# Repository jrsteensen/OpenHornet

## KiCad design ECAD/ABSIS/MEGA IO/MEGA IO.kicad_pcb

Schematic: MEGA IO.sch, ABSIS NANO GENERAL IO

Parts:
C1: 0.1uF; C_0603_HandSoldering
D1, D2, D3: 1N4001; D_1206
J1: PWR; Molex_KK-6410-04_04x2.54mm_Straight
J2: BUS IN; Molex_KK-6410-03_03x2.54mm_Straight
J3: BUS OUT; Molex_KK-6410-03_03x2.54mm_Straight
J4: PWM; Pin_Header_Straight_2x11_Pitch2.54mm
J5: DIG 1; Pin_Header_Straight_2x16_Pitch2.54mm
J6: DIG 2; Pin_Header_Straight_2x16_Pitch2.54mm
J7: A0; Pin_Header_Straight_1x03_Pitch2.54mm
J8: A1; Pin_Header_Straight_1x03_Pitch2.54mm
J9: A2; Pin_Header_Straight_1x03_Pitch2.54mm
J10: A3; Pin_Header_Straight_1x03_Pitch2.54mm
J11: A4; Pin_Header_Straight_1x03_Pitch2.54mm
J12: A5; Pin_Header_Straight_1x03_Pitch2.54mm
J13: A6; Pin_Header_Straight_1x03_Pitch2.54mm
J14: A7; Pin_Header_Straight_1x03_Pitch2.54mm
J15: A8; Pin_Header_Straight_1x03_Pitch2.54mm
J16: A9; Pin_Header_Straight_1x03_Pitch2.54mm
J17: A10; Pin_Header_Straight_1x03_Pitch2.54mm
J18: A11; Pin_Header_Straight_1x03_Pitch2.54mm
J19: A12; Pin_Header_Straight_1x03_Pitch2.54mm
J20: A13; Pin_Header_Straight_1x03_Pitch2.54mm
J21: A14; Pin_Header_Straight_1x03_Pitch2.54mm
J22: A15; Pin_Header_Straight_1x03_Pitch2.54mm
J23: 12V OUT; Pin_Header_Straight_2x03_Pitch2.54mm
J24: COMM; Pin_Header_Straight_2x07_Pitch2.54mm
MK1, MK2, MK3, MK4: Mounting_Hole; MountingHole_4.3mm_M4
P1: Digital; Socket_Strip_Arduino_2x18
P2: Power; Socket_Strip_Arduino_1x08
P3, P4: Analog; Socket_Strip_Arduino_1x08
P5: PWM; Socket_Strip_Arduino_1x10
P6: PWM; Socket_Strip_Arduino_1x08
P7: Communication; Socket_Strip_Arduino_1x08
Q1, Q2, Q3: Q_NMOS_DGS; TO-220-3_Vertical
R1: 120; R_0805_2012Metric_Pad1.15x1.40mm_HandSolder
R2, R3, R4, R5, R6, R7: 1K; R_0805_2012Metric_Pad1.15x1.40mm_HandSolder
SW1: ENABLE; SW_DIP_x4_W6.15mm_Slide_Omron_A6H
U1: MAX487EESA; SOIC-8_3.9x4.9mm_Pitch1.27mm

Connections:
+3V3: J1.2, P2.4
+5V: C1.1, J1.3, J7.2, J8.2, J9.2, J10.2, J11.2, J12.2, J13.2, J14.2, J15.2, J16.2, J17.2, J18.2, J19.2, J20.2, J21.2, J22.2, P1.35, P1.36, P2.5, U1.8 (VCC)
+12V: D1.1 (K), D2.1 (K), D3.1 (K), J1.4, J23.1, J23.3, J23.5, P2.8
/0(Rx0): P6.8, SW1.8
/1(Tx0): P6.7, U1.4 (DI)
/2(**): P6.6, U1.2 (~RE), U1.3 (DE)
/3(**): J4.21, P6.5
/4(**): J4.19, P6.4
/5(**): J4.17, P6.3
/6(**): J4.15, P6.2
/7(**): J4.13, P6.1
/8(**): J4.11, P5.10
/9(**): J4.9, P5.9
/10(**): J4.7, P5.8
/11(**): J4.5, P5.7, SW1.7
/12(**): J4.3, P5.6, SW1.6
/13(**): J4.1, P5.5, SW1.5
/14(Tx3): J24.6, P7.1
/15(Rx3): J24.7, P7.2
/16(Tx2): J24.8, P7.3
/17(Rx2): J24.9, P7.4
/18(Tx1): J24.10, P7.5
/19(Rx1): J24.11, P7.6
/20(SDA): J24.12, P7.7
/21(SCL): J24.13, P7.8
/22: J5.1, P1.33
/23: J5.3, P1.34
/24: J5.5, P1.31
/25: J5.7, P1.32
/26: J5.9, P1.29
/27: J5.11, P1.30
/28: J5.13, P1.27
/29: J5.15, P1.28
/30: J5.17, P1.25
/31: J5.19, P1.26
/32: J5.21, P1.23
/33: J5.23, P1.24
/34: J5.25, P1.21
/35: J5.27, P1.22
/36: J5.29, P1.19
/37: J5.31, P1.20
/38: J6.1, P1.17
/39: J6.3, P1.18
/40: J6.5, P1.15
/41: J6.7, P1.16
/42: J6.9, P1.13
/43: J6.11, P1.14
/44: J6.13, P1.11
/45: J6.15, P1.12
/46: J6.17, P1.9
/47: J6.19, P1.10
/48: J6.21, P1.7
/49: J6.23, P1.8
/50(MISO): J6.25, P1.5
/51(MOSI): J6.27, P1.6
/52(SCK): J6.29, P1.3
/53(SS): J6.31, P1.4
/A0: J7.1, P3.1
/A1: J8.1, P3.2
/A2: J9.1, P3.3
/A3: J10.1, P3.4
/A4: J11.1, P3.5
/A5: J12.1, P3.6
/A6: J13.1, P3.7
/A7: J14.1, P3.8
/A8: J15.1, P4.1
/A9: J16.1, P4.2
/A10: J17.1, P4.3
/A11: J18.1, P4.4
/A12: J19.1, P4.5
/A13: J20.1, P4.6
/A14: J21.1, P4.7
/A15: J22.1, P4.8
/AREF: J24.3, P5.3
/IOREF: J24.4, P2.2
/RX_ENABLE: SW1.1, U1.1 (RO)
/Reset: J24.5, P2.3
/SCL: J24.1, P5.1
/SDA: J24.2, P5.2
GND: C1.2, J1.1, J2.2, J3.2, J4.2, J4.4, J4.6, J4.8, J4.10, J4.12, J4.14, J4.16, J4.18, J4.20, J4.22, J5.2, J5.4, J5.6, J5.8, J5.10, J5.12, J5.14, J5.16, J5.18, J5.20, J5.22, J5.24, J5.26, J5.28, J5.30, J5.32, J6.2, J6.4, J6.6, J6.8, J6.10, J6.12, J6.14, J6.16, J6.18, J6.20, J6.22, J6.24, J6.26, J6.28, J6.30, J6.32, J7.3, J8.3, J9.3, J10.3, J11.3, J12.3, J13.3, J14.3, J15.3, J16.3, J17.3, J18.3, J19.3, J20.3, J21.3, J22.3, J24.14, P1.1, P1.2, P2.6, P2.7, P5.4, Q1.3 (S), Q2.3 (S), Q3.3 (S), R3.1, R5.1, R7.1, U1.5 (GND)
unnamed: D1.2 (A), J23.6, Q3.1 (D)
unnamed: D2.2 (A), J23.4, Q2.1 (D)
unnamed: D3.2 (A), J23.2, Q1.1 (D)
unnamed: J2.1, J3.1, R1.2, U1.6 (A)
unnamed: J2.3, J3.3, R1.1, U1.7 (B)
unnamed: Q1.2 (G), R2.2
unnamed: Q2.2 (G), R4.2
unnamed: Q3.2 (G), R6.2
unnamed: R2.1, R3.2, SW1.2
unnamed: R4.1, R5.2, SW1.3
unnamed: R6.1, R7.2, SW1.4

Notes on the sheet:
Shield for Arduino Mega Rev 3
RS-487 BUS
NOTES: (UNLESS OTHERWISE SPECIFIED)
PWR IN
ANALOG I/O
PWR FLAGS
DIGITAL I/O
COMMUNICATIONS AND MISC
SW1 (ENABLE): POS 1: PGM POS 2: 12V OUT #1 POS 3: 12V OUT #2 POS 4: 12V OUT #3
12V PWM OUT/PGM ENABLE
1) INSTALL 120 OHM RESISTOR ACROSS A AND B OF MAX487 ONLY FOR BUS TERMINATION. 2) TURN DIP SWITCH POS 1 ON FOR RS487 BUS ENABLE. TURN OFF FOR PROGRAMMING ARDUINO NANO. 3) IF 12V OUT #1 IS USED (DIP POS 2 - ON), DO NOT USE DIGITAL I/O POS 11. IF 12V OUT #2 IS USED (DIP POS 3 - ON), DO NOT USE DIGITA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
MOUNTING HOLES

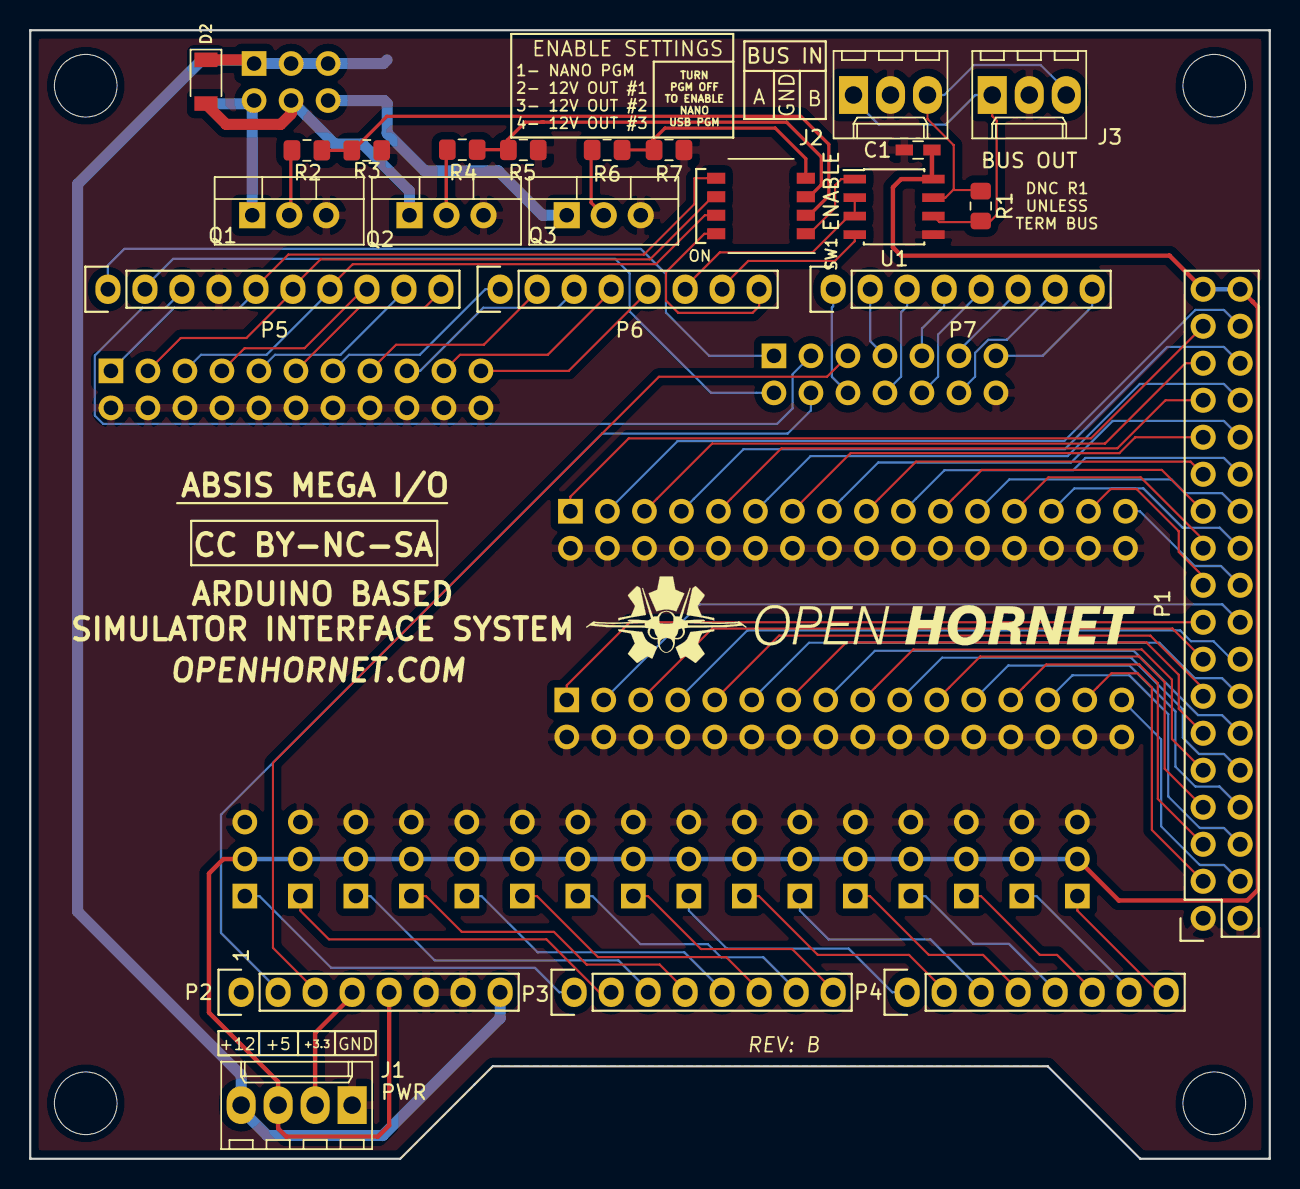
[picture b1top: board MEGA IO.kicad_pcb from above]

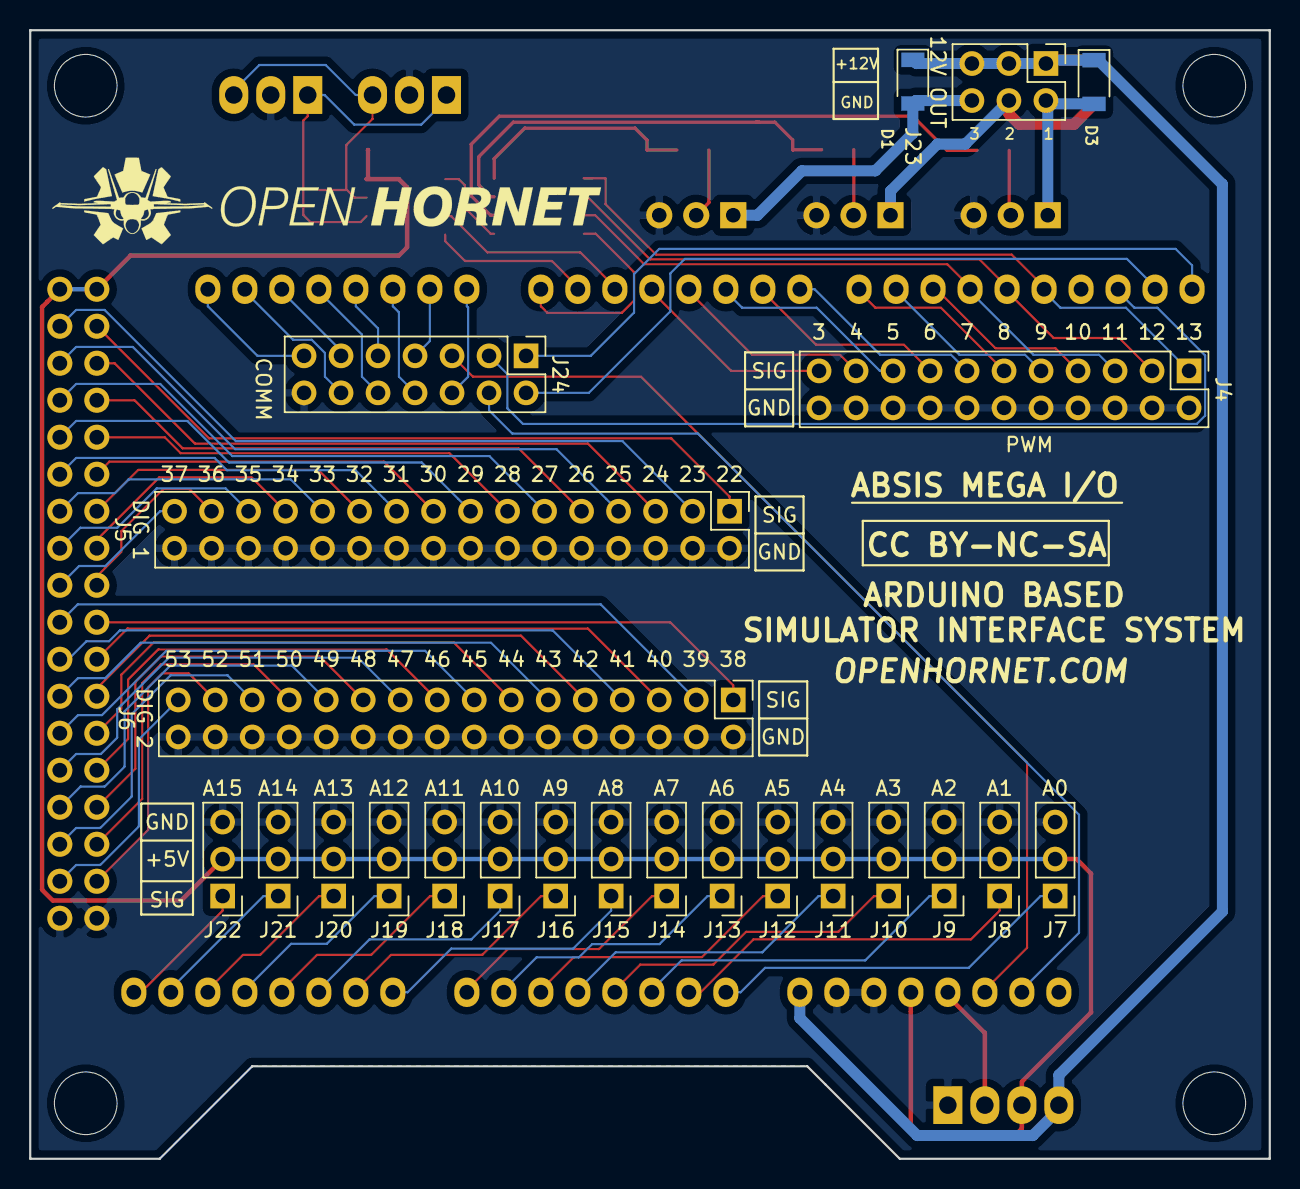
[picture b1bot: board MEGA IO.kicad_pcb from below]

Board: 2 copper layers, 85.1 x 77.5 mm, 51 parts (23 on the bottom side), 91 nets.

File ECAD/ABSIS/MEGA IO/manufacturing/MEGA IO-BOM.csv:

"Id";"Designator";"Package";"Quantity";"Designation";"Supplier and ref";
1;"G***,G***";"OH_LOGO_37.7mm_5.9mm";2;"LOGO";;;
2;"J1";"Molex_KK-6410-04_04x2.54mm_Straight";1;"PWR";;;
3;"C1";"C_0603_HandSoldering";1;"0.1uF";;;
4;"D2,D1,D3";"D_1206";3;"1N4001";;;
5;"J23";"Pin_Header_Straight_2x03_Pitch2.54mm";1;"12V OUT";;;
6;"MK1,MK2,MK3,MK4";"MountingHole_4.3mm_M4";4;"Mounting_Hole";;;
7;"U1";"SOIC-8_3.9x4.9mm_Pitch1.27mm";1;"MAX487EESA";;;
8;"Q2,Q1,Q3";"TO-220-3_Vertical";3;"Q_NMOS_DGS";;;
9;"P1";"Socket_Strip_Arduino_2x18";1;"Digital";;;
10;"P2";"Socket_Strip_Arduino_1x08";1;"Power";;;
11;"P3,P4";"Socket_Strip_Arduino_1x08";2;"Analog";;;
12;"P5";"Socket_Strip_Arduino_1x10";1;"PWM";;;
13;"P6";"Socket_Strip_Arduino_1x08";1;"PWM";;;
14;"P7";"Socket_Strip_Arduino_1x08";1;"Communication";;;
15;"J2";"Molex_KK-6410-03_03x2.54mm_Straight";1;"BUS IN";;;
16;"J3";"Molex_KK-6410-03_03x2.54mm_Straight";1;"BUS OUT";;;
17;"SW1";"SW_DIP_x4_W6.15mm_Slide_Omron_A6H";1;"ENABLE";;;
18;"J4";"Pin_Header_Straight_2x11_Pitch2.54mm";1;"PWM";;;
19;"J5";"Pin_Header_Straight_2x16_Pitch2.54mm";1;"DIG 1";;;
20;"J6";"Pin_Header_Straight_2x16_Pitch2.54mm";1;"DIG 2";;;
21;"J7";"Pin_Header_Straight_1x03_Pitch2.54mm";1;"A0";;;
22;"J8";"Pin_Header_Straight_1x03_Pitch2.54mm";1;"A1";;;
23;"J9";"Pin_Header_Straight_1x03_Pitch2.54mm";1;"A2";;;
24;"J10";"Pin_Header_Straight_1x03_Pitch2.54mm";1;"A3";;;
25;"J11";"Pin_Header_Straight_1x03_Pitch2.54mm";1;"A4";;;
26;"J12";"Pin_Header_Straight_1x03_Pitch2.54mm";1;"A5";;;
27;"J13";"Pin_Header_Straight_1x03_Pitch2.54mm";1;"A6";;;
28;"J14";"Pin_Header_Straight_1x03_Pitch2.54mm";1;"A7";;;
29;"J15";"Pin_Header_Straight_1x03_Pitch2.54mm";1;"A8";;;
30;"J16";"Pin_Header_Straight_1x03_Pitch2.54mm";1;"A9";;;
31;"J17";"Pin_Header_Straight_1x03_Pitch2.54mm";1;"A10";;;
32;"J18";"Pin_Header_Straight_1x03_Pitch2.54mm";1;"A11";;;
33;"J19";"Pin_Header_Straight_1x03_Pitch2.54mm";1;"A12";;;
34;"J20";"Pin_Header_Straight_1x03_Pitch2.54mm";1;"A13";;;
35;"J21";"Pin_Header_Straight_1x03_Pitch2.54mm";1;"A14";;;
36;"J22";"Pin_Header_Straight_1x03_Pitch2.54mm";1;"A15";;;
37;"J24";"Pin_Header_Straight_2x07_Pitch2.54mm";1;"COMM";;;
38;"R1";"R_0805_2012Metric_Pad1.15x1.40mm_HandSolder";1;"120";;;
39;"R2,R3,R4,R5,R6,R7";"R_0805_2012Metric_Pad1.15x1.40mm_HandSolder";6;"1K";;;

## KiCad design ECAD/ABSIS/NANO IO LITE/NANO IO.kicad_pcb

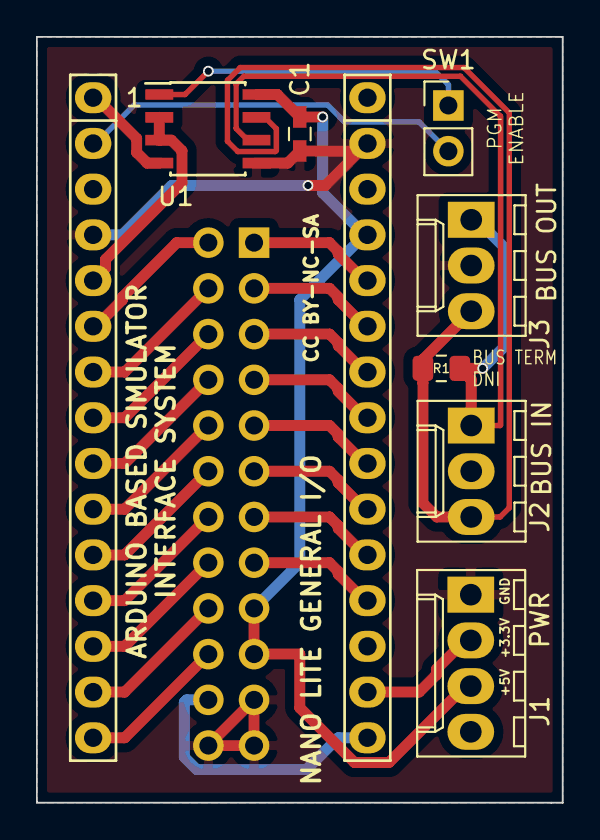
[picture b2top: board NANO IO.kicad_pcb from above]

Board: 2 copper layers, 29.2 x 42.5 mm, 10 parts (1 on the bottom side), 28 nets.

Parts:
C1: 0.1uF; C_0603_HandSoldering
J1: PWR; Molex_KK-6410-04_04x2.54mm_Straight
J2: BUS IN; Molex_KK-6410-03_03x2.54mm_Straight
J3: BUS OUT; Molex_KK-6410-03_03x2.54mm_Straight
J4: I/O; PinHeader_2x12_P2.54mm_Vertical
P1: Digital; Socket_Strip_Arduino_1x15
P2: Analog; Socket_Strip_Arduino_1x15
R1: 120; R_0805_2012Metric_Pad1.15x1.40mm_HandSolder
SW1: ENABLE; PinHeader_1x02_P2.54mm_Vertical
U1: MAX487EESAS; SOIC-8_3.9x4.9mm_Pitch1.27mm

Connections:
+3V3: J1.2, P2.14
+5V: C1.1, J1.3, J4.17, J4.19, P2.4, U1.8
/0(Rx): P1.2, SW1.2
/1(Tx): P1.1, U1.4
/2: P1.5, U1.2, U1.3
/3(**): J4.2, P1.6
/4: J4.4, P1.7
/5(**): J4.6, P1.8
/6(**): J4.8, P1.9
/7: J4.10, P1.10
/8: J4.12, P1.11
/9(**): J4.14, P1.12
/10(**/SS): J4.16, P1.13
/11(**/MOSI): J4.18, P1.14
/12(MISO): J4.20, P1.15
/13(SCK): J4.22, P2.15
/A0: J4.15, P2.12
/A1: J4.13, P2.11
/A2: J4.11, P2.10
/A3: J4.9, P2.9
/A4: J4.7, P2.8
/A5: J4.5, P2.7
/A6: J4.3, P2.6
/A7: J4.1, P2.5
/RX_ENABLE: SW1.1, U1.1
GND: C1.2, J1.1, J2.2, J3.2, J4.21, J4.23, J4.24, P1.4, P2.2, U1.5
unnamed: J2.1, J3.1, R1.2, U1.6
unnamed: J2.3, J3.3, R1.1, U1.7

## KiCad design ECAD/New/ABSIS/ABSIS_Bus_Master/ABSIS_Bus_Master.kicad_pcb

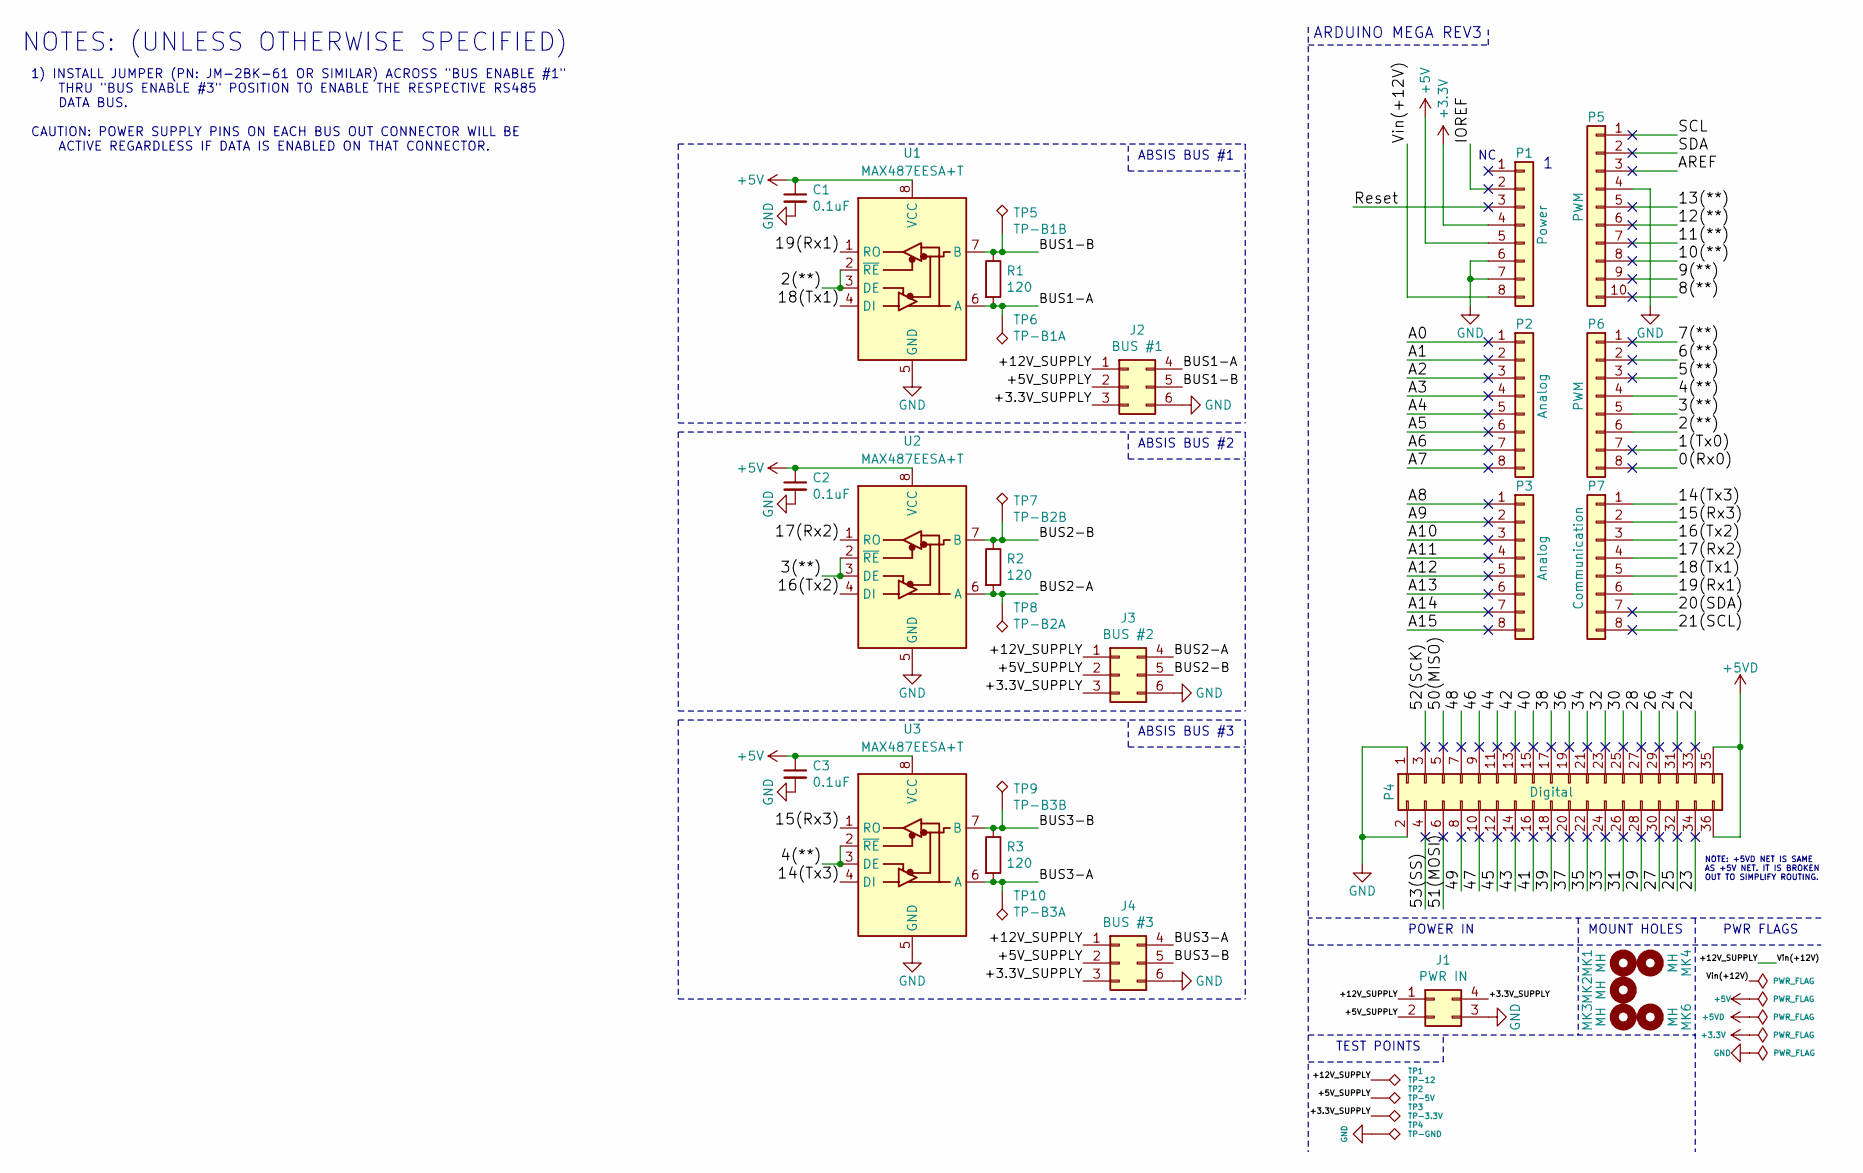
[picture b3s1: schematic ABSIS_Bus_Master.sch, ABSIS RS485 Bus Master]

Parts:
C1, C2, C3: 0.1uF; C_0805_2012Metric_Pad1.15x1.40mm_HandSolder; LCSC C49678
J1: PWR IN; Molex_Micro-Fit_3.0_43045-0412_2x02_P3.00mm_Vertical
J2: BUS #1; Molex_Micro-Fit_3.0_43045-0612_2x03_P3.00mm_Vertical
J3: BUS #2; Molex_Micro-Fit_3.0_43045-0612_2x03_P3.00mm_Vertical
J4: BUS #3; Molex_Micro-Fit_3.0_43045-0612_2x03_P3.00mm_Vertical
MK1, MK2, MK3, MK4, MK6: MH; Arduino_1pin
P1: Power; PinHeader_1x08_P2.54mm_Vertical
P2, P3: Analog; PinHeader_1x08_P2.54mm_Vertical
P4: Digital; PinHeader_2x18_P2.54mm_Vertical
P5: PWM; PinHeader_1x10_P2.54mm_Vertical
P6: PWM; PinHeader_1x08_P2.54mm_Vertical
P7: Communication; PinHeader_1x08_P2.54mm_Vertical
R1, R2, R3: 120; R_0805_2012Metric_Pad1.15x1.40mm_HandSolder; LCSC C17437
TP1: TP-12; TestPoint_THTPad_D1.5mm_Drill0.7mm
TP2: TP-5V; TestPoint_THTPad_D1.5mm_Drill0.7mm
TP3: TP-3.3V; TestPoint_THTPad_D1.5mm_Drill0.7mm
TP4: TP-GND; TestPoint_THTPad_D1.5mm_Drill0.7mm
TP5: TP-B1B; TestPoint_THTPad_D1.5mm_Drill0.7mm
TP6: TP-B1A; TestPoint_THTPad_D1.5mm_Drill0.7mm
TP7: TP-B2B; TestPoint_THTPad_D1.5mm_Drill0.7mm
TP8: TP-B2A; TestPoint_THTPad_D1.5mm_Drill0.7mm
TP9: TP-B3B; TestPoint_THTPad_D1.5mm_Drill0.7mm
TP10: TP-B3A; TestPoint_THTPad_D1.5mm_Drill0.7mm
U1, U2, U3: MAX487EESA+T; SOIC-8_3.9x4.9mm_P1.27mm; LCSC C116539

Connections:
+3V3: P1.4
+5V: C1.1, C2.1, C3.1, P1.5, U1.8 (VCC), U2.8 (VCC), U3.8 (VCC)
+5VD: P4.35, P4.36
/0(Rx0): P6.8
/1(Tx0): P6.7
/2(**): P6.6, U1.2 (~RE), U1.3 (DE)
/3(**): P6.5, U2.2 (~RE), U2.3 (DE)
/4(**): P6.4, U3.2 (~RE), U3.3 (DE)
/5(**): P6.3
/6(**): P6.2
/7(**): P6.1
/8(**): P5.10
/9(**): P5.9
/10(**): P5.8
/11(**): P5.7
/12(**): P5.6
/13(**): P5.5
/14(Tx3): P7.1, U3.4 (DI)
/15(Rx3): P7.2, U3.1 (RO)
/16(Tx2): P7.3, U2.4 (DI)
/17(Rx2): P7.4, U2.1 (RO)
/18(Tx1): P7.5, U1.4 (DI)
/19(Rx1): P7.6, U1.1 (RO)
/20(SDA): P7.7
/21(SCL): P7.8
/22: P4.33
/23: P4.34
/24: P4.31
/25: P4.32
/26: P4.29
/27: P4.30
/28: P4.27
/29: P4.28
/30: P4.25
/31: P4.26
/32: P4.23
/33: P4.24
/34: P4.21
/35: P4.22
/36: P4.19
/37: P4.20
/38: P4.17
/39: P4.18
/40: P4.15
/41: P4.16
/42: P4.13
/43: P4.14
/44: P4.11
/45: P4.12
/46: P4.9
/47: P4.10
/48: P4.7
/49: P4.8
/50(MISO): P4.5
/51(MOSI): P4.6
/52(SCK): P4.3
/53(SS): P4.4
/+3.3V_SUPPLY: J1.4, J2.3, J3.3, J4.3, TP3.1
/+5V_SUPPLY: J1.2, J2.2, J3.2, J4.2, TP2.1
/+12V_SUPPLY: J1.1, J2.1, J3.1, J4.1, P1.8, TP1.1
/A0: P2.1
/A1: P2.2
/A2: P2.3
/A3: P2.4
/A4: P2.5
/A5: P2.6
/A6: P2.7
/A7: P2.8
/A8: P3.1
/A9: P3.2
/A10: P3.3
/A11: P3.4
/A12: P3.5
/A13: P3.6
/A14: P3.7
/A15: P3.8
/AREF: P5.3
/BUS1-A: J2.4, R1.2, TP6.1, U1.6 (A)
/BUS1-B: J2.5, R1.1, TP5.1, U1.7 (B)
/BUS2-A: J3.4, R2.2, TP8.1, U2.6 (A)
/BUS2-B: J3.5, R2.1, TP7.1, U2.7 (B)
/BUS3-A: J4.4, R3.2, TP10.1, U3.6 (A)
/BUS3-B: J4.5, R3.1, TP9.1, U3.7 (B)
/IOREF: P1.2
/Reset: P1.3
/SCL: P5.1
/SDA: P5.2
GND: C1.2, C2.2, C3.2, J1.3, J2.6, J3.6, J4.6, P1.6, P1.7, P4.1, P4.2, P5.4, TP4.1, U1.5 (GND), U2.5 (GND), U3.5 (GND)

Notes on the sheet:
ABSIS BUS #1
ABSIS BUS #2
ABSIS BUS #3
1) INSTALL JUMPER (PN: JM-2BK-61 OR SIMILAR) ACROSS "BUS ENABLE #1" THRU "BUS ENABLE #3" POSITION TO ENABLE THE RESPECTIVE RS485 DATA BUS. CAUTION: POWER SUPPLY PINS ON EACH BUS OUT CONNECTOR WILL BE ACTIVE REGARDLESS IF DATA IS ENABLED ON THAT CONNECTOR.
ARDUINO MEGA REV3
NOTES: (UNLESS OTHERWISE SPECIFIED)
MOUNT HOLES
NOTE: +5VD NET IS SAME AS +5V NET. IT IS BROKEN OUT TO SIMPLIFY ROUTING.
PWR FLAGS
POWER IN
TEST POINTS

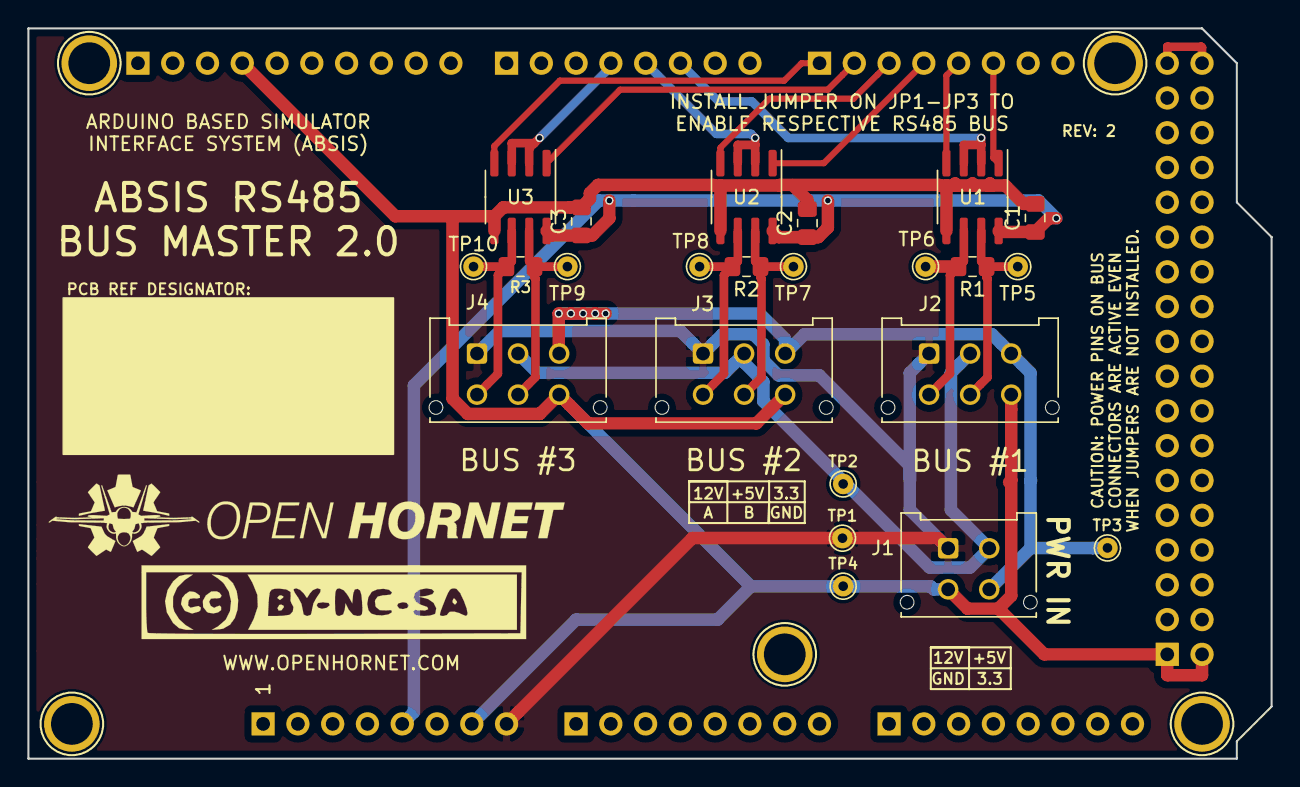
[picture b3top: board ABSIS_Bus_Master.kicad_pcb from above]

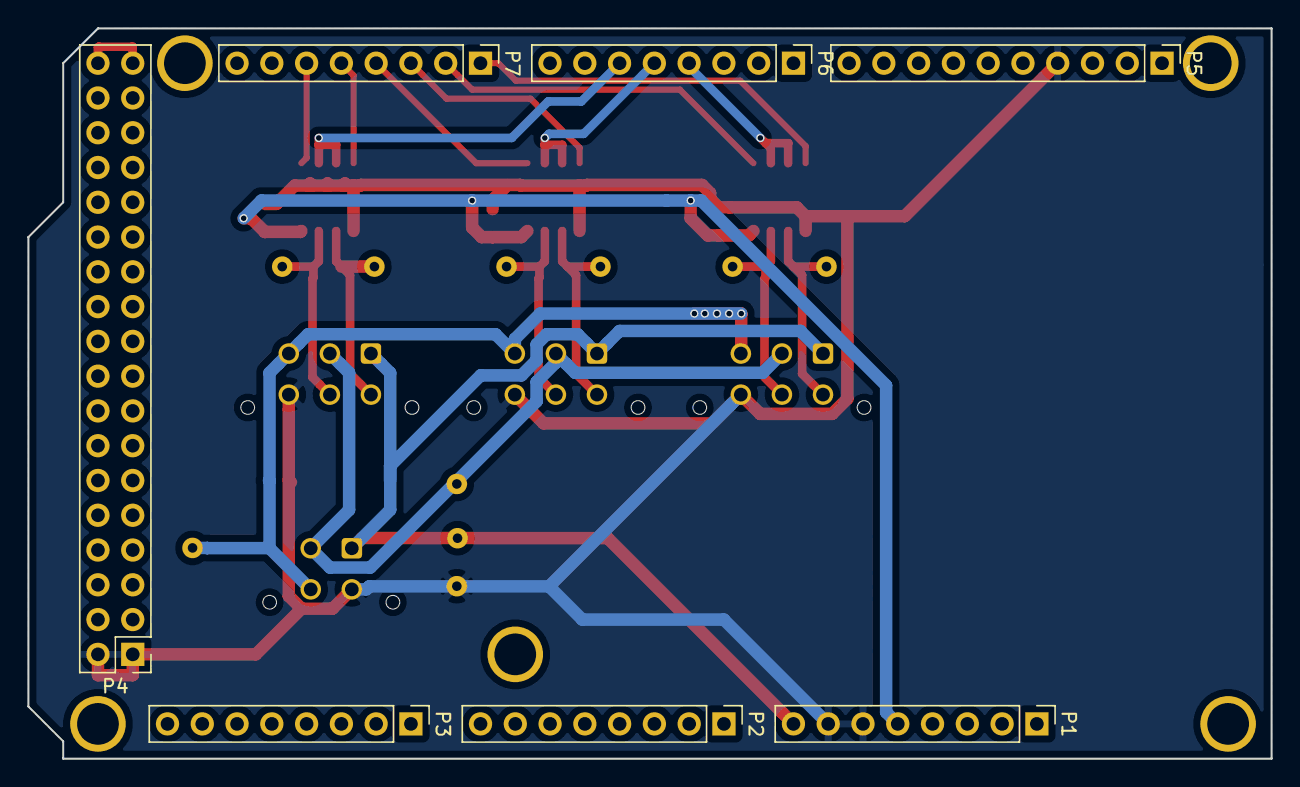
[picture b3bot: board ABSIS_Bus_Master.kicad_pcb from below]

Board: 2 copper layers, 90.8 x 53.3 mm, 35 parts (7 on the bottom side), 21 nets.

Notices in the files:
ECAD/ABSIS/MEGA IO/MEGA IO.kicad_pcb:
CC BY-NC-SA
ECAD/New/ABSIS/ABSIS_Bus_Master/ABSIS_Bus_Master.sch:
License: CC BY-NC-SA
